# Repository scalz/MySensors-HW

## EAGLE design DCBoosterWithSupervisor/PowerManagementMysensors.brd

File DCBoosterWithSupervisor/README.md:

# DCBoosterWithSupervisor 

It is a small board with only DCBooster3V and 2V Supervisor for power management. It can be used to add functionality in Mysensorsnodes. 

still in dev

TODO : 
- add pin description
- add Bill of Materials
- add gerbers for Seeed, Itead, and OSH fabhouses.
- custom bootloader

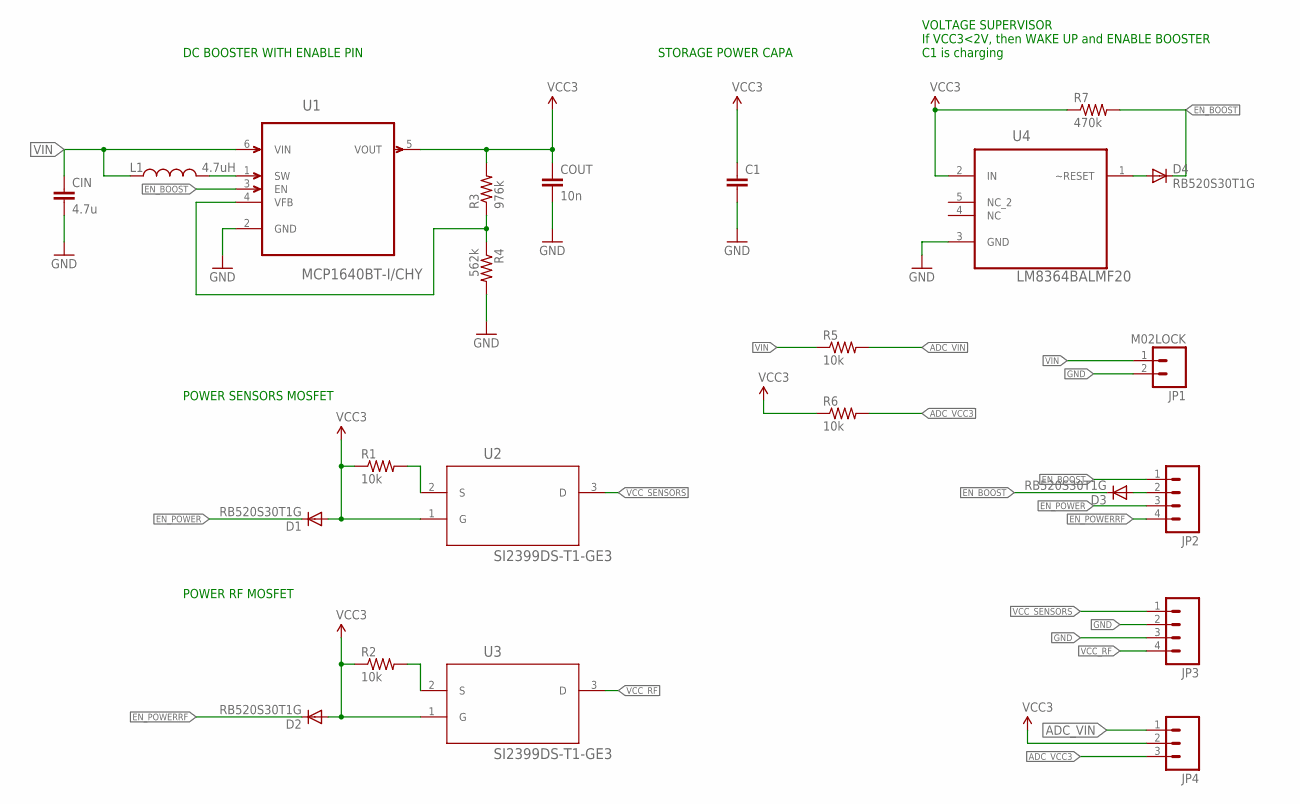
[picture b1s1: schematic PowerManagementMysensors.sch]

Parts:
C1: CAP1206; 1206
CIN: 4.7u; 1206
COUT: 10n; 1206
D1, D2, D3, D4: RB520S30T1G; SOD523
JP1: M02LOCK; 1X02_LOCK
JP2: M04LOCK; 1X04_LOCK
JP3: M041X04_NO_SILK; 1X04_NO_SILK
JP4: M03LOCK; 1X03_LOCK
L1: 4.7uH; 1210
R1, R2, R5, R6: 10k; 1206
R3: 976k; 1206
R4: 562k; 1206
R7: 470k; 1206
U1: MCP1640BT-I/CHY; SOT95P270X145-6N
U2, U3: SI2399DS-T1-GE3; SOT95P237X112-3N
U4: LM8364BALMF20; SOT95P284X122-5N

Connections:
ADC_VCC3: JP4.3, R6.2
ADC_VIN: JP4.1, R5.2
EN_BOOST: D3.C, D4.C, JP2.1, R7.2, U1.3 (EN)
EN_POWER: D1.C, JP2.3
EN_POWERRF: D2.C, JP2.4
GND: C1.2, CIN.2, COUT.2, JP1.2, JP3.2, JP3.3, R4.2, U1.2 (GND), U4.3 (GND)
unnamed: L1.2, U1.1 (SW)
unnamed: R1.2, U2.2 (S)
unnamed: R3.1, R4.1, U1.4 (VFB)
unnamed: D4.A, U4.1 (~RESET)
unnamed: D3.A, JP2.2
unnamed: R2.2, U3.2 (S)
VCC: C1.1, COUT.1, D1.A, D2.A, JP4.2, R1.1, R2.1, R3.2, R6.1, R7.1, U1.5 (VOUT), U2.1 (G), U3.1 (G), U4.2 (IN)
VCC_RF: JP3.4, U3.3 (D)
VCC_SENSORS: JP3.1, U2.3 (D)
VIN: CIN.1, JP1.1, L1.1, R5.1, U1.6 (VIN)

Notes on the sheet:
DC BOOSTER WITH ENABLE PIN
STORAGE POWER CAPA
VOLTAGE SUPERVISOR If VCC3<2V, then WAKE UP and ENABLE BOOSTER C1 is charging
POWER SENSORS MOSFET
POWER RF MOSFET

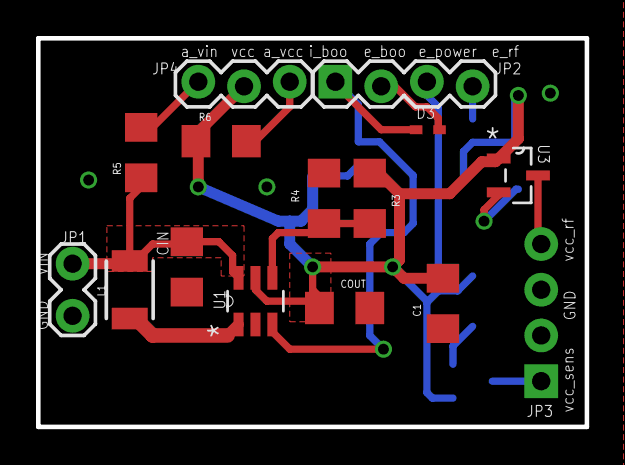
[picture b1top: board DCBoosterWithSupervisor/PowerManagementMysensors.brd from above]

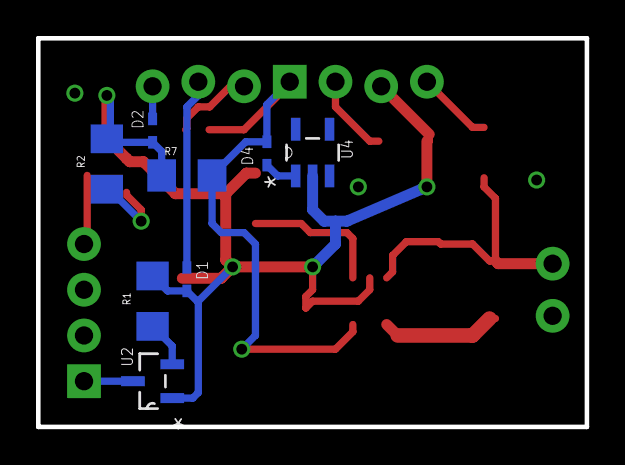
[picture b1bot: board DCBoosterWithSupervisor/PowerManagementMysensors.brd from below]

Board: 2 copper layers, 30.5 x 21.6 mm, 23 parts (8 on the bottom side), 16 nets.

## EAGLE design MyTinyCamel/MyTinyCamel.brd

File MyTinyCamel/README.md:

# MyTinyCamel

Based on my previous PowerManagement. I have miniaturized it.

Size : 49.5x23.8 (mm)
Components size 0805.

####Sensors Node with power management features : 
- power through VBAT directly
- power through 3V Dc booster
- mode ultra low power ( < 1uA in sleep mode) needs the onboard 3VDC booster
- power through MCP1703 for VIN < 16V
- Mosfet for radio
- Mosfet for sensors
- Atmel 328p
- two DC boosters 3V and 5V
- onboard MCP1703 regulator
- supervisory circuit (2v threshold) 
- 3 optional i2c connectors. Each one has its 3v (through mosfet), 5V, GND
- MYSXconnector 1.5 to plug external boards/sensors
- rfm69hw/nrf24 smd footprints
- ATSHA for authentication
- external eeprom for OTA
- optional onnboard LED
- onboard optional i2c pullups
- optional pullups for IO
- Smd jumpers.

####Jumper settings :
- JP1 : VIN selection (power directly from VIN/VBAT | 3V DC Booster | MCP1703 
- JP2 : if JP1 is set VIN/VBAT, so you can choose if you want VIN/VBAT only, or if you want to use MCP1703
- JP3 : if JP1 is set on 3VDC Booster, you can enable storage capacitor for ultra low power mode 
- JP4 : enable/disable 5VDC Booster
- JP5 : if set, enable voltage supervisor control for ultra low power mode
- JP6 : choose if you want to power external eeprom through mosfet VCC sensors or through regulated VCC3 directly
- JP7 : choose if you want to power radios through mosfet VCC RF or through regulated VCC3 directly
- JP8 : choose INT2 Mode : INT2 or Interrupt on 2V supervisor (if 2v, wake up arduino, enable dc booster to charge C1) 
- JP9 : how 3VDC booster is enabled. By Supervisor/atmel pins or by VIN for continuous mode

####Atmel Pinout :
- A1 : Output : Enable/disable RF VCC 
- A2 : ADC Input used for reading battery voltage (<5v)
- D3 : optional INT2 or for voltage supervisor control
- D4 : Output : Enable/disable Sensors 3V Rail 
- D5 : Output : enable/disable DC Boost 3v

####MYSXConnector 1.5 : 
- 1 :	VIN connected to -> batt vs dc booster vs MCP1703 3.3vreg (max16v)
- 2 :	VCC3
- 3 :	VCCIO
- 4 :	GND
- 5 :	TX
- 6 :	RX
- 7 :	A6
- 8 :	A7
- 9 :	D2
- 10 :	D3
- 11 :	D5
- 12 :	D6
- 13 :	SCL
- 14 :	SDA
- 15 :	A0
- 16 :	D8
- 17 :	MOSI
- 18 :	MISO
- 19 :	SCK
- 20 :	D7

### Board overview  

&nbsp; 

####TODO : 
- settings description
- some coding
...

Note : it is still in dev. there are some issues which will be fixed in next rev soon

####Links, reference and license : 

Copyright scalz (2015). released under the [CERN Open Hardware Licence v1.2](http://ohwr.org/cernohl)

This board is inspired from the great work of :
- Patrick Fallberg : https://github.com/fallberg/MySensorsNode

Copyright Patrick Fallberg (2015). CERN Open Hardware Licence v1.2](http://ohwr.org/cernohl)

- Charles-Henri Hallard : https://hallard.me/category/ulpnode/
 
Copyright Charles-Henri Hallard (2014). [Attribution-ShareAlike CC BY-SA](https://creativecommons.org/licenses/)

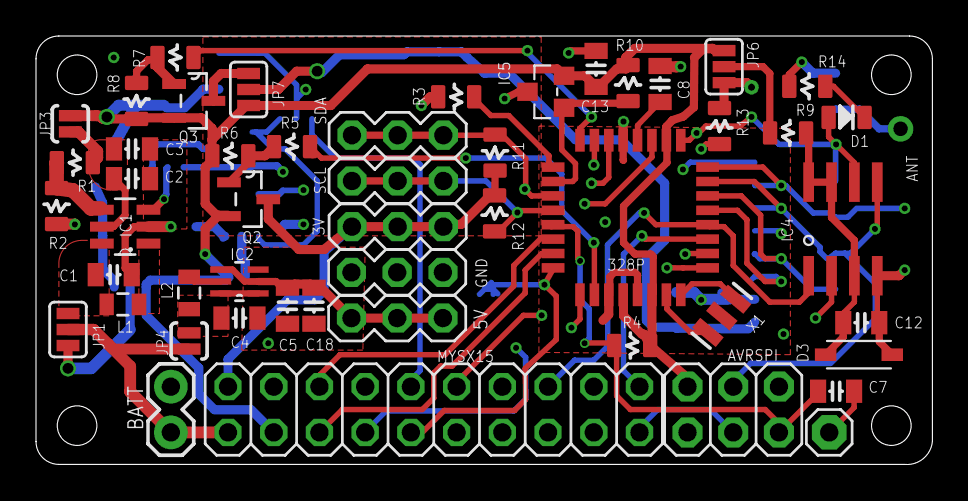
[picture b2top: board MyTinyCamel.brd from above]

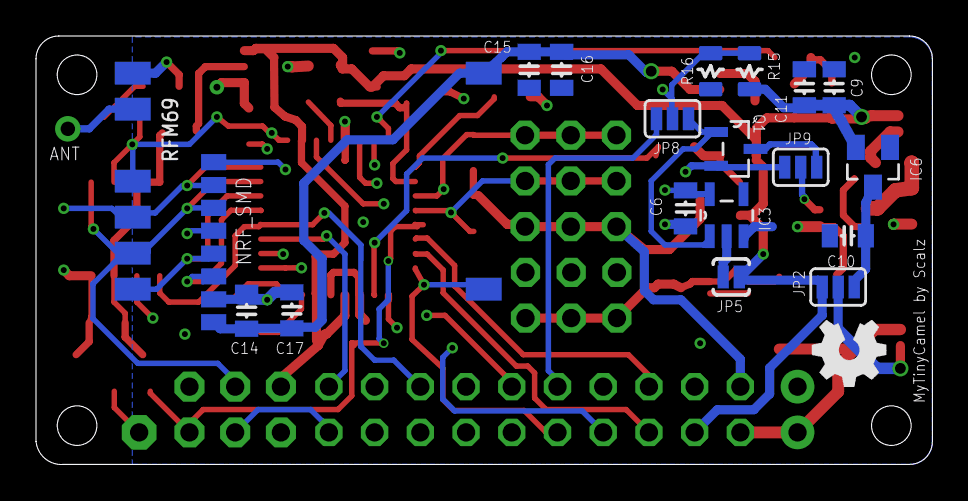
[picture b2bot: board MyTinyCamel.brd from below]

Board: 4 copper layers, 49.8 x 23.8 mm, 70 parts (19 on the bottom side), 53 nets.

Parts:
3V, 5V: 1X03
328P: ATMega-328; TQFP32-08
ANT: RFM12B_ANTENNA; RFM12B-ANTENNA
AVRSPI: AVRSPI; 2X03
BATT: M02PTH; 1X02
C1: 4.7u; 0805-CAP
C2: 10n; 0805-CAP
C3: 0805-CAP
C4, C5, C11: 10u; 0805-CAP
C6: 33n; 0805-CAP
C7, C8, C9: 0.1; 0805-CAP
C10: 1u; 0805-CAP
C12, C13: 100n; 0805-CAP
C14, C15: 4u7; 0805-CAP
C16, C17, C18: 0.1u; 0805-CAP
D1: LED0805; 0805-LED
D3: BZT52H-B3V6; SOD-123
DTR: 1X01
GND: 1X03
IC1: MCP1640T-I/CHY; SOT95P270X145-6N
IC2: TPS61222DCKT; SOT65P210X110-6N
IC3: NCP302LSN20T1
IC4: AT25DF512C-SSHN-B; SO-08
IC5: ATSHA204A; SOT23
IC6: MCP1703CB; SOT23
JP1, JP2, JP6, JP7, JP8, JP9: JUMPER-3SMD; SJ_3
JP3, JP4, JP5: SJ_2S-NO
L1, L2: 4.7uH; 0805
MYSX15: MYSXConnector 1.5; 2X10
NRF_SMD: NRF24L01+SMD_MODULE
Q1: cj2305; SOT95P237X112-3N
Q2, Q3: SI2399DS-T1-GE3; SOT95P237X112-3N
R1: 976k; 0805-RES
R2: 562k; 0805-RES
R3: 0805-RES
R4, R6, R8, R13, R15, R16: 10k; 0805-RES
R5, R7, R9: 100; 0805-RES
R10: 56k; 0805-RES
R11, R12: 4k7; 0805-RES
R14: 330; 0805-RES
RFM69: RFM69; RFM69W-MINPADS
SCL: 1X03
SDA: 1X03
X1: 8 MHz; RESONATOR-SMD

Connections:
A0: 328P.23, MYSX15.15
A1: 328P.24, R7.1
A2: 328P.25, R3.2
A3: 328P.26, IC5.1, R10.1
ADC1: 328P.19, MYSX15.7
ADC2: 328P.22, MYSX15.8
AREF: 328P.20, C8.1
D2: 328P.32, MYSX15.9, NRF_SMD.IRQ, RFM69.DIO0
D3: 328P.1, JP8.2, R15.1, R16.1
D4: 328P.2, R5.1
D5: 328P.9, C6.1, IC3.CD, MYSX15.11
D6: 328P.10, MYSX15.12, R13.1
D7: 328P.11, MYSX15.20
D9: 328P.13, NRF_SMD.CE
D10: 328P.14, NRF_SMD.CSN, RFM69.NSS
DTR: C7.1, DTR.1
EN_BOOST: IC1.3, JP9.2
FLASH_CSN: 328P.12, IC4.1, MYSX15.16
GND: 328P.3, 328P.5, 328P.21, AVRSPI.6, BATT.2, C1.2, C2.2, C3.2, C4.2, C5.2, C6.2, C8.2, C9.2, C10.2, C11.2, C12.2, C13.1, C14.1, C15.1, C16.1, C17.1, C18.2, D3.A, GND.1, GND.2, GND.3, IC1.2, IC2.3, IC3.GND, IC4.4, IC5.3, IC6.1, MYSX15.4, NRF_SMD.GND, R2.2, R14.2, R16.2, RFM69.GND, X1.2
INT2: JP8.3, MYSX15.10
INT_BOOST: IC3.RST, JP8.1, Q1.1
MISO: 328P.16, AVRSPI.1, IC4.2, MYSX15.18, NRF_SMD.MISO, RFM69.MISO
MOSI: 328P.15, AVRSPI.4, IC4.5, MYSX15.17, NRF_SMD.MOSI, RFM69.MOSI
unnamed: IC1.1, L1.2
unnamed: ANT.P$1, RFM69.ANA
unnamed: IC3.IN, JP5.1
unnamed: IC1.4, R1.1, R2.1
unnamed: JP6.2, R9.2
unnamed: C12.1, D3.C, IC4.3, IC4.7, IC4.8, R9.1
unnamed: Q2.1, R5.2, R6.1
unnamed: C2.1, C3.1, IC1.5, JP3.1, R1.2
unnamed: 328P.7, X1.1
unnamed: IC2.5, L2.2
unnamed: D1.MINUS, R14.1
unnamed: C4.1, IC2.1, IC2.6, JP4.1, L2.1
unnamed: JP1.3, JP2.2
unnamed: Q3.1, R7.2, R8.1
unnamed: 328P.8, X1.3
Q_NCP: JP9.1, Q1.3
RST: 328P.29, AVRSPI.5, C7.2, R4.1
RX: 328P.30, MYSX15.6
SCK: 328P.17, AVRSPI.3, D1.PLUS, IC4.6, MYSX15.19, NRF_SMD.SCK, RFM69.SCK
SCL: 328P.28, MYSX15.13, R12.1, SCL.1, SCL.2, SCL.3
SDA: 328P.27, MYSX15.14, R11.1, SDA.1, SDA.2, SDA.3
TX: 328P.31, MYSX15.5
V+5: 5V.1, 5V.2, 5V.3, C5.1, C18.1, IC2.2, IC2.4
VCC: 328P.4, 328P.6, 328P.18, AVRSPI.2, C9.1, C11.1, C13.2, IC5.2, IC6.2, JP2.3, JP3.2, JP5.2, JP6.3, JP7.3, MYSX15.3, Q2.2, Q3.2, R4.2, R6.2, R8.2, R10.2, R15.2
VCCRF: C14.2, C15.2, C16.2, C17.2, JP7.2, NRF_SMD.3V, RFM69.VDD
VCC_RF: JP7.1, Q3.3
VCC_SENSORS: 3V.1, 3V.2, 3V.3, JP6.1, MYSX15.2, Q2.3, R11.2, R12.2, R13.2
VIN: BATT.1, JP1.2, JP4.2, JP9.3, MYSX15.1, Q1.2, R3.1
VIN2: C1.1, IC1.6, JP1.1, L1.1
VREG: C10.1, IC6.3, JP2.1

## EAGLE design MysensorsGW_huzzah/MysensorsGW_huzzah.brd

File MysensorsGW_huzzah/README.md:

# MysensorsGW_huzzah

Small Mysensors WIFI/MQTT Gateway project.

Project still in dev.

- Huzzah Esp8266 pin compatible
- NRF24 and RFM69 smd footprint
- ATSHA204A authentication footprint

TODO : 
- add pin description
- add Bill of Materials
- add gerbers for Seeed, Itead, and OSH fabhouses.
- add esp8266 GW sketch

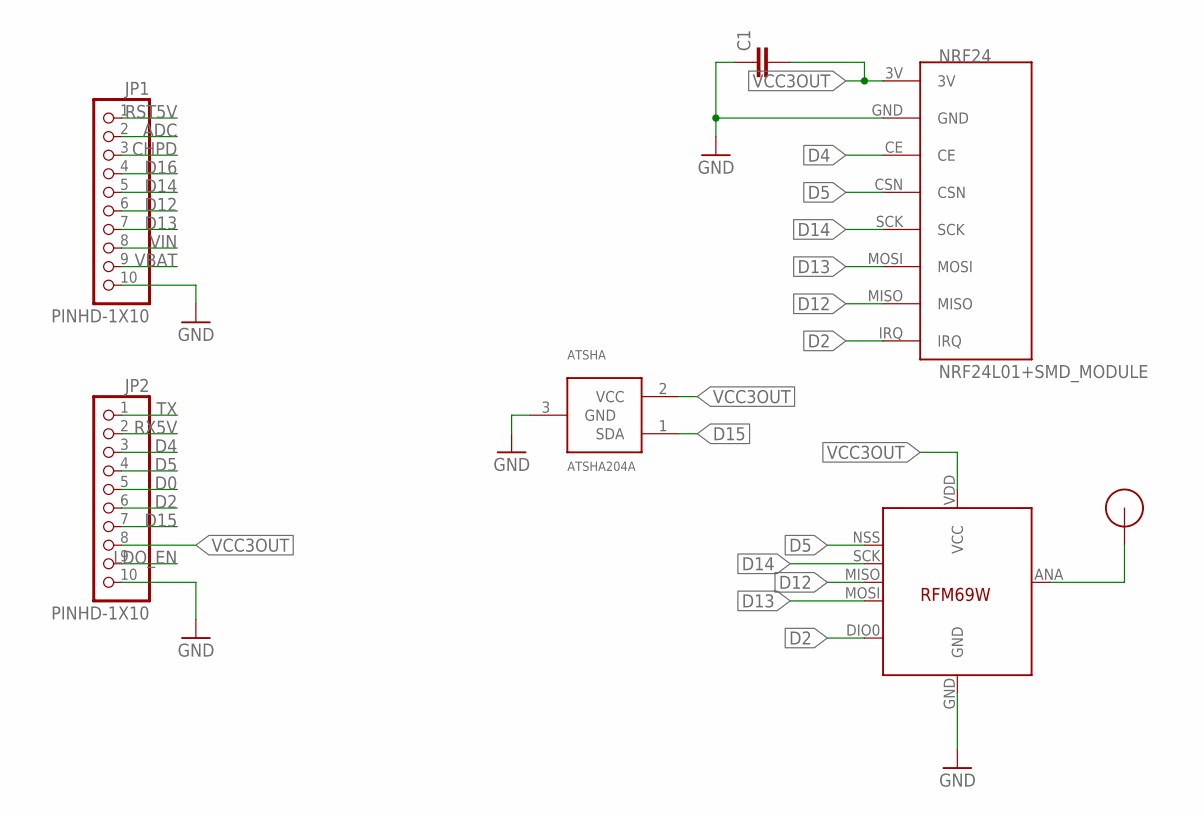
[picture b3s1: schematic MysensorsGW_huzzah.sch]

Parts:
ATSHA: ATSHA204A; SOT23
C1: CAP1206; 1206
JP1, JP2: PINHD-1X10; 1X10-BIG
NRF24: NRF24L01+SMD_MODULE
RFM69: RFM69; RFM69W-MINPADS
U$2: RFM12B_ANTENNA; RFM12B-ANTENNA

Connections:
ADC: JP1.2
CHPD: JP1.3
D0: JP2.5
D2: JP2.6, NRF24.IRQ, RFM69.DIO0
D4: JP2.3, NRF24.CE
D5: JP2.4, NRF24.CSN, RFM69.NSS (SEL)
D12: JP1.6, NRF24.MISO, RFM69.MISO
D13: JP1.7, NRF24.MOSI, RFM69.MOSI
D14: JP1.5, NRF24.SCK, RFM69.SCK
D15: ATSHA.1 (SDA), JP2.7
D16: JP1.4
GND: ATSHA.3 (GND), C1.1, JP1.10, JP2.10, NRF24.GND, RFM69.GND
LDO_EN: JP2.9
unnamed: RFM69.ANA (ANT), U$2.P$1
RST5V: JP1.1
RX5V: JP2.2
TX: JP2.1
VBAT: JP1.9
VCC3OUT: ATSHA.2 (VCC), C1.2, JP2.8, NRF24.3V, RFM69.VDD (VCC)
VIN: JP1.8

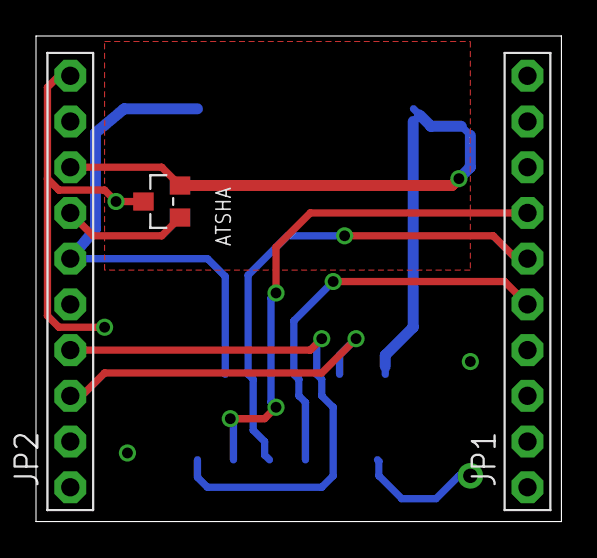
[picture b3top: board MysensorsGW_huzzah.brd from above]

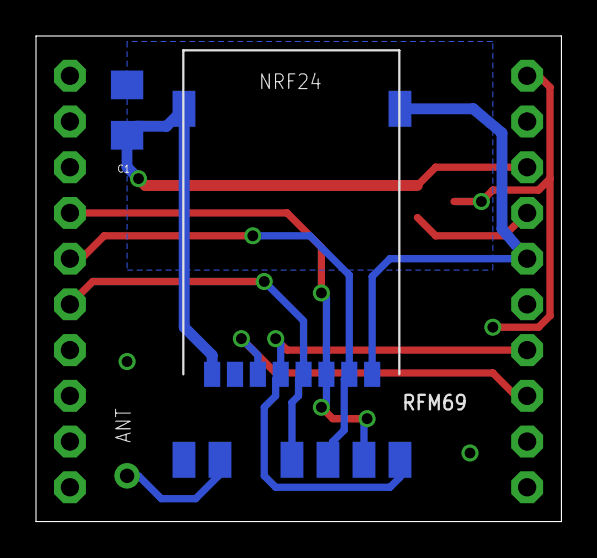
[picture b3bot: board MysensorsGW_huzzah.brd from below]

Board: 2 copper layers, 29.2 x 27.0 mm, 7 parts (3 on the bottom side), 10 nets.

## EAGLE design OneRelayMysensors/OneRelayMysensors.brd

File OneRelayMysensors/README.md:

# OneRelayMysensors

A simple, basic, board to control one relais for Mysensors. still in dev (waiting for pcb)

- Atmel 328p
- NRF24 and RFM69 footprint
- ATSHA204A authentication footprint
- AVRSPI connector
- FTDI connector
- ACS712 footprint
- 10 A Relay footprint
- need transformer to power the board

TODO : 
- add pin description
- add Bill of Materials
- add gerbers for Seeed, Itead, and OSH fabhouses.

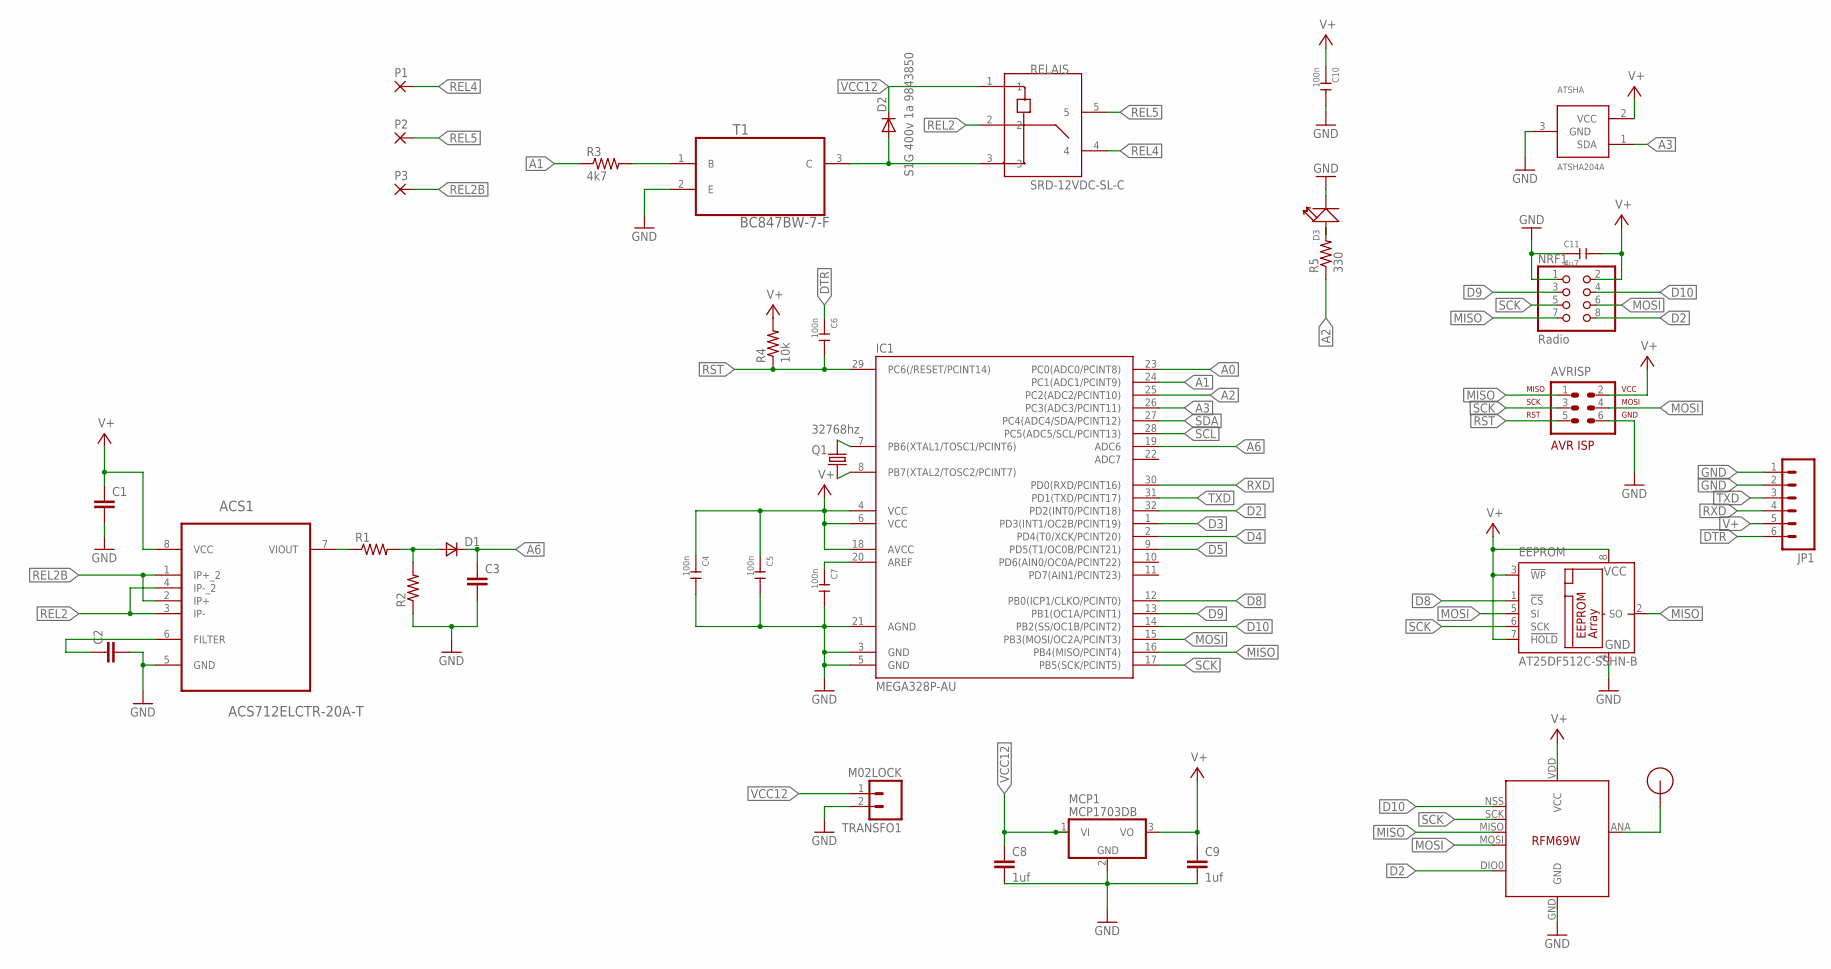
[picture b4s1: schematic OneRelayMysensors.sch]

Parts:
$1_28_$: RFM12B_ANTENNA; RFM12B-ANTENNA
ACS1: ACS712ELCTR-20A-T; SOIC127P600X175-8N
ATSHA: ATSHA204A; SOT23
AVRISP: AVR-ISP-6VERT; AVR-ISP-6
C1, C2, C3: CAP0805; 0805
C4, C5, C6, C7, C10: 100n; C1206
C8, C9: 1uf; 1206
C11: 4u7; C1206
D1: DSOD323; SOD323
D2: S1G 400v 1a 9843850; DO214AC
D3: LED-0805
EEPROM: AT25DF512C-SSHN-B; SO-08
IC1: MEGA328P-AU; TQFP32-08
JP1: M06NO_SILK_FEMALE_PTH; 1X06_NO_SILK
MCP1: MCP1703DB; SOT223
NRF1: Radio; 2X04
P1, P2, P3: 2,54/1,1
Q1: 32768hz; 2P-L3.2XW1.5MM
R1, R2: RESISTOR0805-RES; 0805
R3: 4k7; 1206
R4: 10k; 1206
R5: 330; 1206
RELAIS: SRD-12VDC-SL-C
RFM1: RFM69; RFM69W-MINPADS
T1: BC847BW-7-F; SOT65P210X110-3N
TRANSFO1: M02LOCK; 1X02_LOCK

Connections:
A0: IC1.23 (PC0(ADC0/PCINT8))
A1: IC1.24 (PC1(ADC1/PCINT9)), R3.1
A2: IC1.25 (PC2(ADC2/PCINT10)), R5.1
A3: ATSHA.1 (SDA), IC1.26 (PC3(ADC3/PCINT11))
A6: C3.1, D1.1 (C), IC1.19 (ADC6)
D2: IC1.32 (PD2(INT0/PCINT18)), NRF1.8, RFM1.DIO0
D3: IC1.1 (PD3(INT1/OC2B/PCINT19))
D4: IC1.2 (PD4(T0/XCK/PCINT20))
D5: IC1.9 (PD5(T1/OC0B/PCINT21))
D8: EEPROM.1 (!CS), IC1.12 (PB0(ICP1/CLKO/PCINT0))
D9: IC1.13 (PB1(OC1A/PCINT1)), NRF1.3
D10: IC1.14 (PB2(SS/OC1B/PCINT2)), NRF1.4, RFM1.NSS (SEL)
DTR: C6.1, JP1.6
GND: ACS1.5 (GND), ATSHA.3 (GND), AVRISP.6, C1.2, C2.2, C3.2, C4.2, C5.2, C7.2, C8.2, C9.2, C10.2, C11.1, D3.-, EEPROM.4 (GND), IC1.3 (GND), IC1.5 (GND), IC1.21 (AGND), JP1.1, JP1.2, MCP1.2 (GND), NRF1.1, R2.1, RFM1.GND, T1.2 (E), TRANSFO1.2
MISO: AVRISP.1, EEPROM.2 (SO), IC1.16 (PB4(MISO/PCINT4)), NRF1.7, RFM1.MISO
MOSI: AVRISP.4, EEPROM.5 (SI), IC1.15 (PB3(MOSI/OC2A/PCINT3)), NRF1.6, RFM1.MOSI
unnamed: IC1.7 (PB6(XTAL1/TOSC1/PCINT6)), Q1.1
unnamed: IC1.8 (PB7(XTAL2/TOSC2/PCINT7)), Q1.2
unnamed: D3.+, R5.2
unnamed: C7.1, IC1.20 (AREF)
unnamed: $1_28_$.P$1, RFM1.ANA (ANT)
unnamed: D2.A, RELAIS.3, T1.3 (C)
unnamed: R3.2, T1.1 (B)
unnamed: ACS1.6 (FILTER), C2.1
unnamed: ACS1.7 (VIOUT), R1.1
unnamed: D1.2 (A), R1.2, R2.2
REL2: ACS1.3 (IP-), ACS1.4 (IP-_2), RELAIS.2
REL2B: ACS1.1 (IP+_2), ACS1.2 (IP+), P3.1
REL4: P1.1, RELAIS.4
REL5: P2.1, RELAIS.5
RST: AVRISP.5, C6.2, IC1.29 (PC6(/RESET/PCINT14)), R4.1
RXD: IC1.30 (PD0(RXD/PCINT16)), JP1.4
SCK: AVRISP.3, EEPROM.6 (SCK), IC1.17 (PB5(SCK/PCINT5)), NRF1.5, RFM1.SCK
SCL: IC1.28 (PC5(ADC5/SCL/PCINT13))
SDA: IC1.27 (PC4(ADC4/SDA/PCINT12))
TXD: IC1.31 (PD1(TXD/PCINT17)), JP1.3
V+: ACS1.8 (VCC), ATSHA.2 (VCC), AVRISP.2, C1.1, C4.1, C5.1, C9.1, C10.1, C11.2, EEPROM.3 (!WP), EEPROM.7 (!HOLD), EEPROM.8 (VCC), IC1.4 (VCC), IC1.6 (VCC), IC1.18 (AVCC), JP1.5, MCP1.3 (VO), NRF1.2, R4.2, RFM1.VDD (VCC)
VCC12: C8.1, D2.C, MCP1.1 (VI), RELAIS.1, TRANSFO1.1

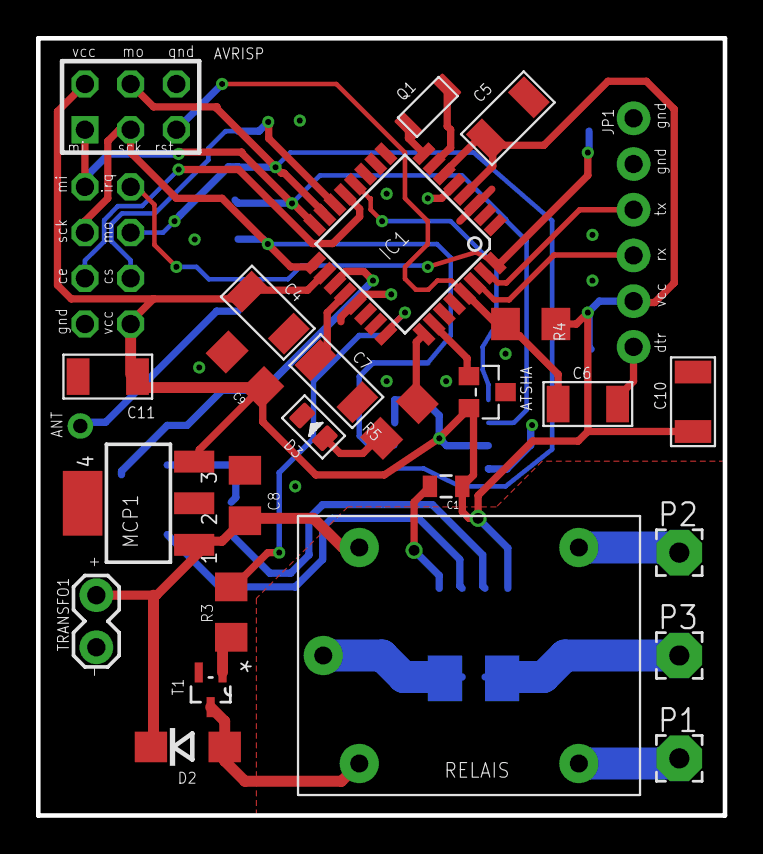
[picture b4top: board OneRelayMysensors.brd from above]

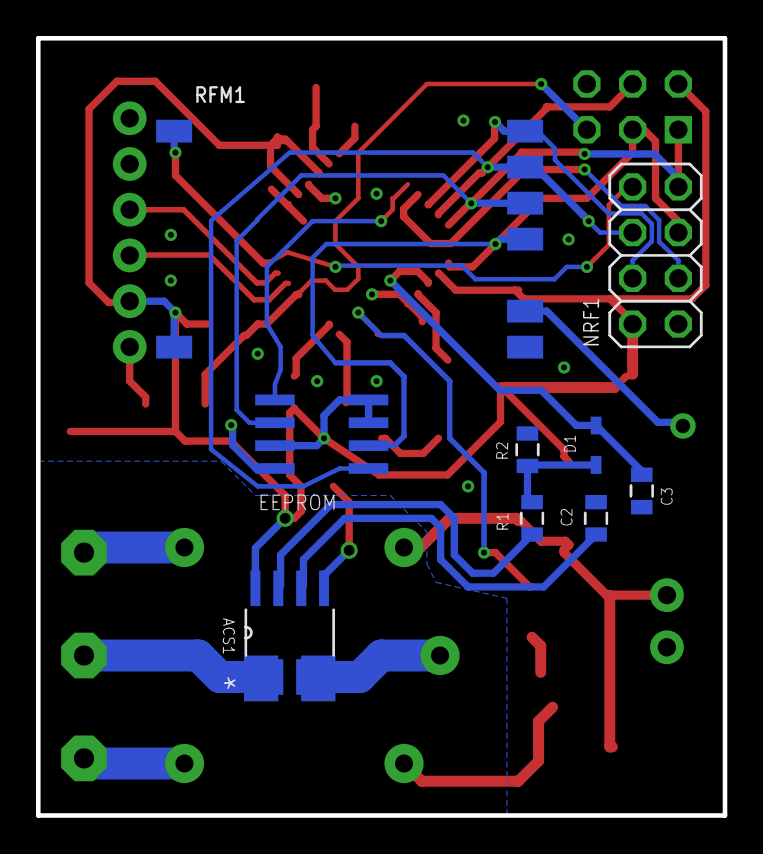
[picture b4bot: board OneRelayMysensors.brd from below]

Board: 2 copper layers, 38.2 x 43.2 mm, 36 parts (9 on the bottom side), 32 nets.

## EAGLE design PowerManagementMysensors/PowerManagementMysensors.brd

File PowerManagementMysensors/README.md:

# PowerManagementMysensors

I mixed Anticimex(Patrick Fallberg) SensorsNode (in dev) with functionalities of ulpnode, to fit my needs. All credits to them for concepts and idea (links below). Here is my version still in dev.

Size : 50x44 (mm)

PowerManagementMysensors : nrf24/RFM69

PowerManagementMysensors2 : nrf24 smd module/RFM69

- Arduino pro mini connector

- C1 : Storage capacitor if using Ultra Low power Node 
- JP1, JP2 : Power by VIN, Bypass DC Boost 3v and capa c1 
- JP3 : enable/disable DC Booster +5V 
- JP4 : enable/disable 2v supervisor and its interrupt 
- JP5 : choose INT2 Mode : INT2 or Interrupt on 2V supervisor (if 2v, wake up arduino, enable dc booster to charge C1) 
- JP6 : Radio CSN Pin NRF or RFM69 
- JP7 : choose INT1 mode : INT1 or INT NRF connection

- A0 PIN : ADC Input used for reading C1 voltage 
- A1 PIN : Output : Enable/disable RF VCC 
- A2 PIN : ADC Input used for reading battery voltage (<5v)
- D4 PIN : Output : Enable/disable Sensors 3V Rail 
- D5 PIN : Output : enable/disable DC Boost 3v

Connectors :
- +3V Sensors
- +5V
- GND
- J1 : free. connected to TX
- J2 : free. connected to RX
- J3 : free. connected to D3 INT2 (jumper config)
- J4 : free. connected to D6. PWM
- J5 : free. connected to A6. ADC1
- J6 : free. connected to A7. ADC2
- J7 : I2C1 (A4 SDA, A5 SCL)
- J8 : I2C2 (A4 SDA, A5 SCL)
- J9 : free. SPI CSN. connected to D7.
- J10 : free. connected to D2. INT1 (jumper config)

- FLASH for OTA
- ATSHA204A authentication
- NRF24 or RFM69 footprint 
- AVRSPI connector
- I2C pull ups on board

How it will work :

1) Basic Mode : You can enable/disable functions, dc boosters, supervisor, power directly from battery... See jumpers and connectors description

2) Ulpnode mode : Enable JP1, JP2, JP4, JP5 supervisor

To get ultra low power, it needs : 
- not use watchdog so you can save uA
- to wake up, use pin change interrupt
- no bod during sleep mode
- lower voltage frequency. So, BOD=1.8V, sleep mode freq : 1-4Mhz.
So, to be able to wake up each period, when supervisor < 2v, it toggles interrupt EN_BOOST, so dc Booster 3v starts to charge C1, and arduino wakes up. As the supervisor will maintain interrupt while vcc<2v, you can maintain interrupt by enabling D5 output Arduino and check the C1 voltage level by reading A0 arduino. Then do your tasks (tune frequ clock, enable rf and sensors power, readings...), then tune freq for sleeping, disable D5 and you can put arduino in sleep mode again. C1 will discharge from 3.3v to <2v (need to test C1 value to know discharge time). And again...

it is possible to monitor battery voltage. But be careful, as I didn't want to consume more power with traditional divider, and have not enough free output to disable by mosfet such divider, 
I have choosen to use simple ADC read through resistor. Batt voltage must be <= vcc arduino to be able to read. I added protection for eeprom.

Note : it is still in dev. so not tested. I will make some changes I think.

TODO : 
- add gerbers for Seeed, Itead, and OSH fabhouses.
- custom bootloader

Links, reference and license : 

Copyright scalz (2015). [Attribution-ShareAlike CC BY-SA](https://creativecommons.org/licenses/)

- For https://github.com/fallberg/MySensorsNode,

Copyright Patrick Fallberg (2015). All designs are released under the [CERN Open Hardware Licence v1.2](http://ohwr.org/cernohl)

- For https://hallard.me/category/ulpnode/, 

Copyright Charles-Henri Hallard (2014). [Attribution-ShareAlike CC BY-SA](https://creativecommons.org/licenses/)

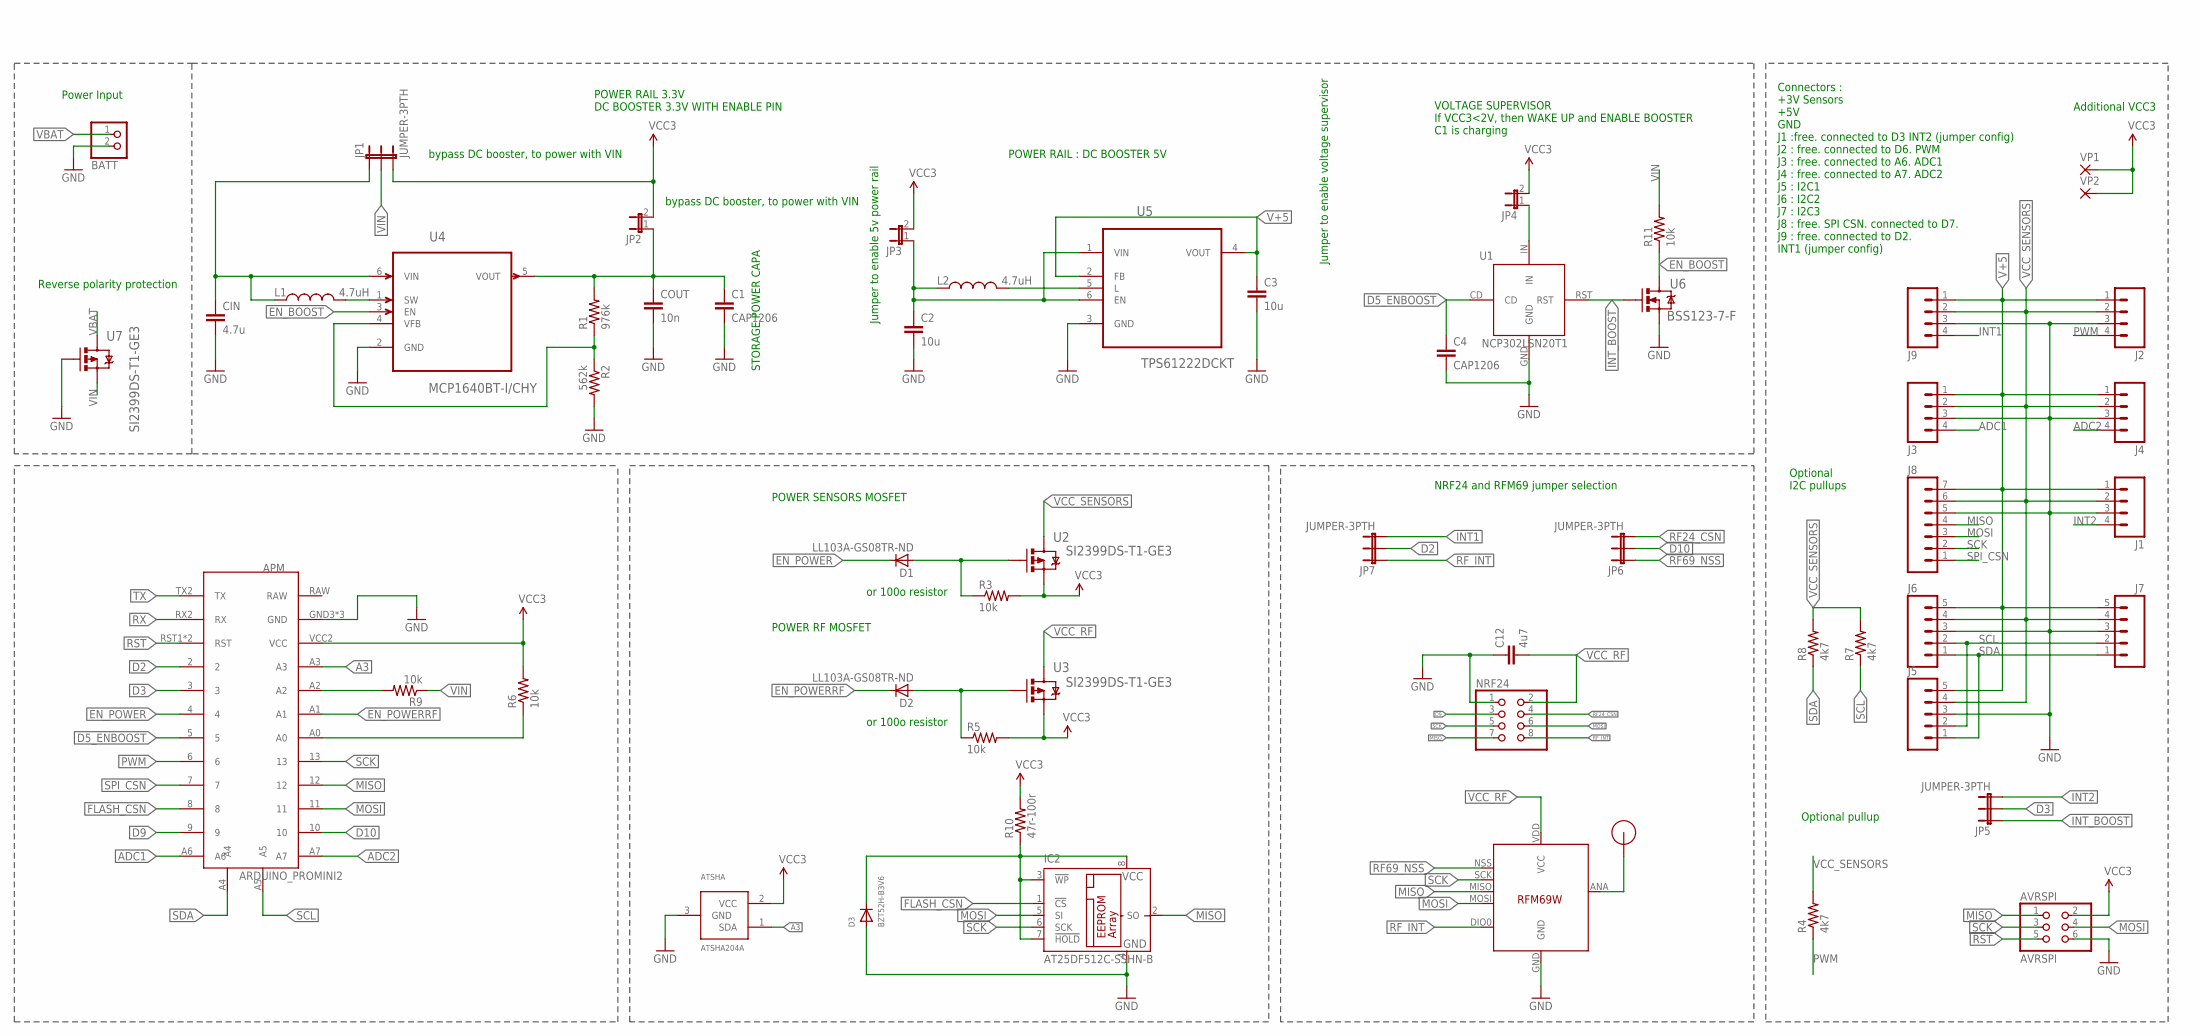
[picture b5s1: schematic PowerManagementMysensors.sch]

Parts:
ANT: RFM12B_ANTENNA; RFM12B-ANTENNA
APM: ARDUINO_PROMINI2
ATSHA: ATSHA204A; SOT23
AVRSPI: AVRSPI; 2X03
BATT: JST_2PIN-THM; JST-PH-2-THM
C1, C4: CAP1206
C2, C3: 10u; CAP1206
C12: 4u7; CAP1206
CIN: 4.7u; CAP1206
COUT: 10n; CAP1206
D1, D2: LL103A-GS08TR-ND; SOD80
D3: BZT52H-B3V6; SOD-123
IC2: AT25DF512C-SSHN-B; SO-08
J1, J2, J3, J4, J9: M041X04_NO_SILK; 1X04_NO_SILK
J5, J6, J7: M05NO_SILK; 1X05_NO_SILK
J8: M07; 1X07
JP1, JP5, JP6, JP7: JUMPER-3PTH; 1X03
JP2, JP3, JP4: JUMPER-2PTH; 1X02
L1, L2: 4.7uH; 0805
NRF24: PINHD-2X4; 2X04
R1: 976k; 1206
R2: 562k; 1206
R3, R5, R6, R9, R11: 10k; 1206
R4, R7, R8: 4k7; 1206
R10: 47r-100r; 1206
RFM69: RFM69; RFM69W-MINPADS
U1: NCP302LSN20T1
U2, U3, U7: SI2399DS-T1-GE3; SOT95P237X112-3N
U4: MCP1640BT-I/CHY; SOT95P270X145-6N
U5: TPS61222DCKT; SOT65P210X110-6N
U6: BSS123-7-F; SOT95P240X110-3N
VP1, VP2: 1,6/0,9

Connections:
A3: APM.A3, ATSHA.1 (SDA)
ADC1: APM.A6, J3.4
ADC2: APM.A7, J4.4
D2: APM.2, JP7.2
D3: APM.3, JP5.2
D5_ENBOOST: APM.5, C4.1, U1.CD
D9: APM.9, NRF24.3
D10: APM.10, JP6.2
EN_BOOST: R11.1, U4.3 (EN), U6.3 (D)
EN_POWER: APM.4, D1.1 (C)
EN_POWERRF: APM.A1, D2.1 (C)
FLASH_CSN: APM.8, IC2.1 (!CS)
GND: APM.GND3 (GND), APM.GND4 (GND), APM.GND5 (GND), ATSHA.3 (GND), AVRSPI.6, BATT.2 (1), C1.2, C2.2, C3.2, C4.2, C12.1, CIN.2, COUT.2, D3.A, IC2.4 (GND), J1.3, J2.3, J3.3, J4.3, J5.3, J6.3, J7.3, J8.5, J9.3, NRF24.1, R2.2, RFM69.GND, U1.GND, U4.2 (GND), U5.3 (GND), U6.2 (S), U7.1 (G)
INT1: J9.4, JP7.3
INT2: J1.4, JP5.3
INT_BOOST: JP5.1, U1.RST, U6.1 (G)
MISO: APM.12, AVRSPI.1, IC2.2 (SO), J8.4, NRF24.7, RFM69.MISO
MOSI: APM.11, AVRSPI.4, IC2.5 (SI), J8.3, NRF24.6, RFM69.MOSI
unnamed: L1.2, U4.1 (SW)
unnamed: ANT.P$1, RFM69.ANA (ANT)
unnamed: JP4.1, U1.IN
unnamed: R1.1, R2.1, U4.4 (VFB)
unnamed: D3.C, IC2.3 (!WP), IC2.7 (!HOLD), IC2.8 (VCC), R10.1
unnamed: D1.2 (A), R3.1, U2.1 (G)
unnamed: C1.1, COUT.1, JP2.1, R1.2, U4.5 (VOUT)
unnamed: L2.2, U5.5 (L)
unnamed: APM.A0, R6.1
unnamed: C2.1, JP3.1, L2.1, U5.1 (VIN), U5.6 (EN)
unnamed: APM.A2, R9.2
unnamed: D2.2 (A), R5.1, U3.1 (G)
PWM: APM.6, J2.4, R4.1
RF24_CSN: JP6.3, NRF24.4
RF69_NSS: JP6.1, RFM69.NSS (SEL)
RF_INT: JP7.1, NRF24.8, RFM69.DIO0
RST: APM.RST1 (RST), APM.RST2 (RST), AVRSPI.5
RX: APM.RX2 (RX)
SCK: APM.13, AVRSPI.3, IC2.6 (SCK), J8.2, NRF24.5, RFM69.SCK
SCL: APM.A5, J5.2, J6.2, J7.2, R7.1
SDA: APM.A4, J5.1, J6.1, J7.1, R8.1
SPI_CSN: APM.7, J8.1
TX: APM.TX2 (TX)
V+5: C3.1, J1.1, J2.1, J3.1, J4.1, J5.5, J6.5, J7.5, J8.7, J9.1, U5.2 (FB), U5.4 (VOUT)
VBAT: BATT.1 (2), U7.3 (D)
VCC: APM.VCC2 (VCC), ATSHA.2 (VCC), AVRSPI.2, JP1.3, JP2.2, JP3.2, JP4.2, R3.2, R5.2, R6.2, R10.2, U2.2 (S), U3.2 (S), VP1.1, VP2.1
VCC_RF: C12.2, NRF24.2, RFM69.VDD (VCC), U3.3 (D)
VCC_SENSORS: J1.2, J2.2, J3.2, J4.2, J5.4, J6.4, J7.4, J8.6, J9.2, R4.2, R7.2, R8.2, U2.3 (D)
VIN: JP1.2, R9.1, R11.2, U7.2 (S)
VIN2: CIN.1, JP1.1, L1.1, U4.6 (VIN)

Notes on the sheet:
POWER RAIL 3.3V DC BOOSTER 3.3V WITH ENABLE PIN
STORAGE POWER CAPA
VOLTAGE SUPERVISOR If VCC3<2V, then WAKE UP and ENABLE BOOSTER C1 is charging
POWER SENSORS MOSFET
POWER RF MOSFET
POWER RAIL : DC BOOSTER 5V
bypass DC booster, to power with VIN
Jumper to enable 5v power rail
Jumper to enable voltage supervisor
Connectors : +3V Sensors +5V GND J1 :free. connected to D3 INT2 (jumper config) J2 : free. connected to D6. PWM J3 : free. connected to A6. ADC1 J4 : free. connected to A7. ADC2 J5 : I2C1 J6 : I2C2 J7 : I2C3 J8 : free. SPI CSN. connected to D7. J9 : free. connected to D2. INT1 (jumper config)
or 100o resistor
Power Input
Reverse polarity protection
NRF24 and RFM69 jumper selection
Additional VCC3
Optional I2C pullups
Optional pullup

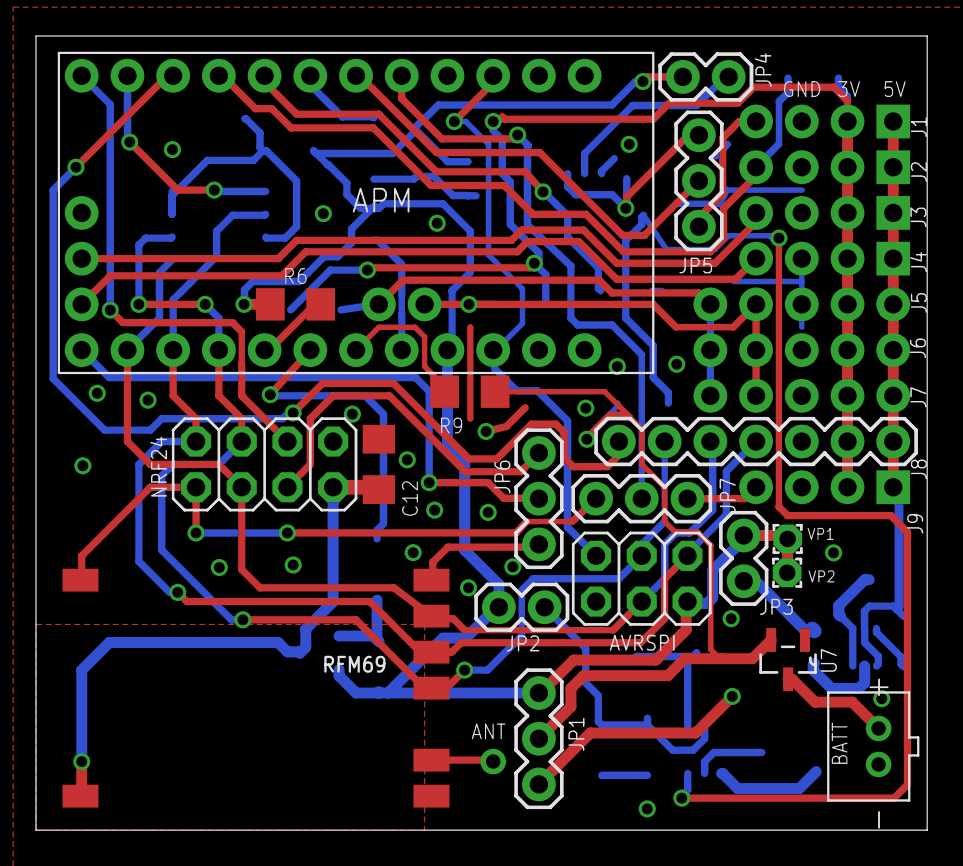
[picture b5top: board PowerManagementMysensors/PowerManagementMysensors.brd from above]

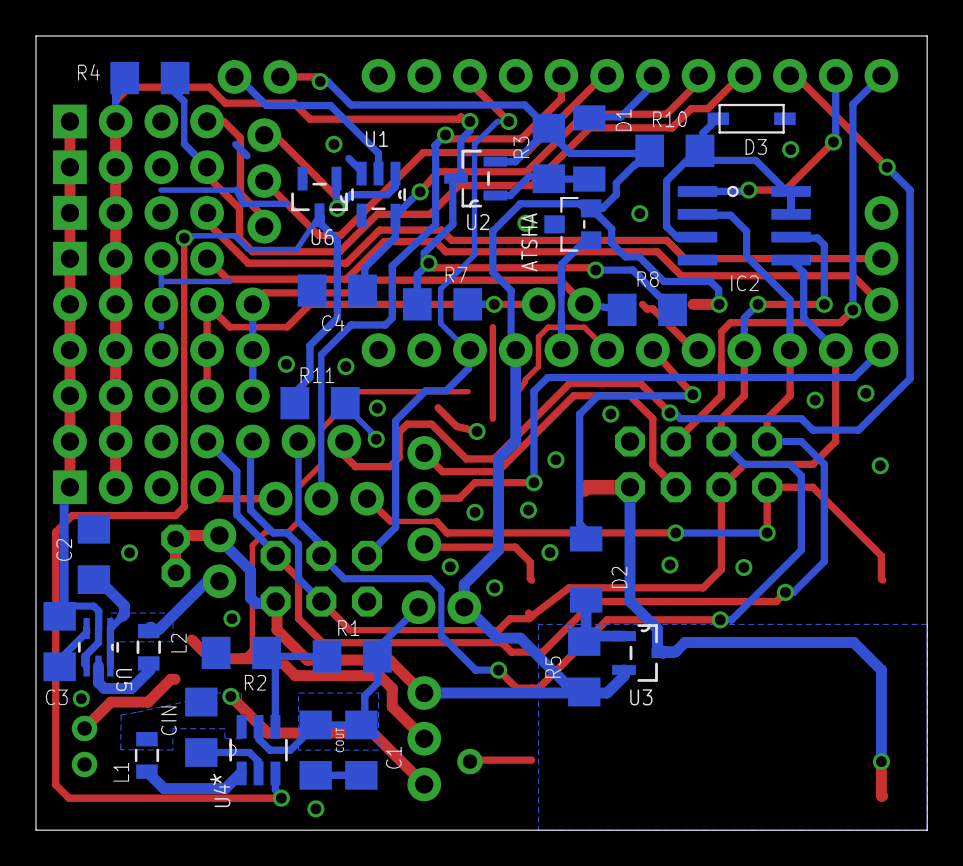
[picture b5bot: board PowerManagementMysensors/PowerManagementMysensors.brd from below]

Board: 2 copper layers, 49.5 x 44.1 mm, 56 parts (28 on the bottom side), 46 nets.

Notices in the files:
parts and their libraries:
SparkFun-Passives: Licensing: Creative Commons ShareAlike 4.0 International - https://creativecommons.org/licenses/by-sa/4.0
